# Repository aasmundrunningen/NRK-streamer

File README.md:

# NRK-streamer
A computer with a HDMI switch connected so that you can play NRK with one button press and switch to another HDMI input using a HDMI-switch

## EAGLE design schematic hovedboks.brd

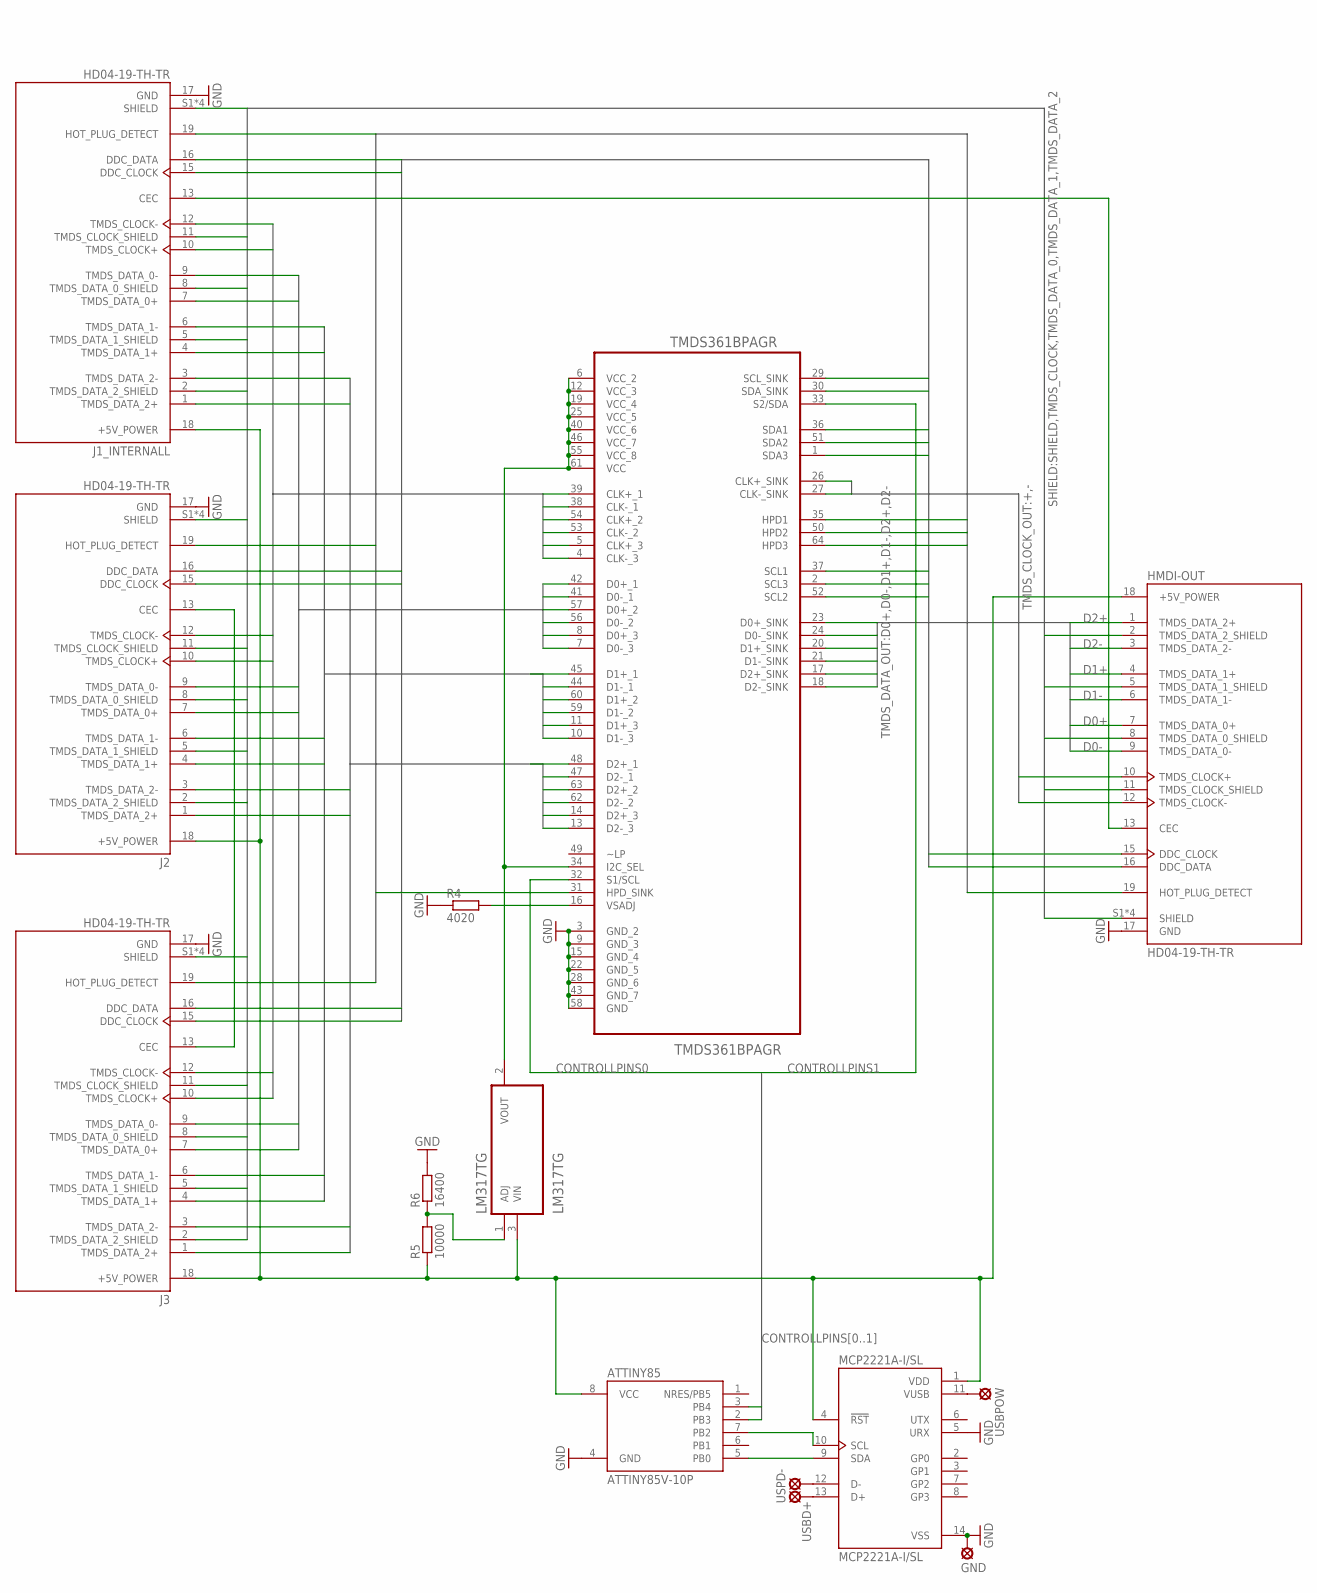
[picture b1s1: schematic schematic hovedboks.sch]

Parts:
ATTINY85: ATTINY85V-10P; PDIP08_300MIL
GND: LSP10
HMDI-OUT: HD04-19-TH-TR; CUI_HD04-19-TH-TR
J1_INTERNALL, J2, J3: HD04-19-TH-TR; CUI_HD04-19-TH-TR
LM317TG: LM317TG; TO254P1054X470X1955-3
MCP2221A-I/SL: MCP2221A-I/SL; SOIC127P600X175-14N
R4: 4020; 0204/7
R5: 10000; 0204/7
R6: 16400; 0204/7
TMDS361BPAGR: TMDS361BPAGR; QFP50P1200X1200X120-64N
USBD+: LSP10
USBPOW: LSP10
USPD-: LSP10

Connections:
1: J1_INTERNALL.19 (HOT_PLUG_DETECT), TMDS361BPAGR.35 (HPD1)
1_CLOCK: J1_INTERNALL.15 (DDC_CLOCK), TMDS361BPAGR.37 (SCL1)
1_DATA: J1_INTERNALL.16 (DDC_DATA), TMDS361BPAGR.36 (SDA1)
2: J2.19 (HOT_PLUG_DETECT), TMDS361BPAGR.50 (HPD2)
2_CLOCK: J2.15 (DDC_CLOCK), TMDS361BPAGR.2 (SCL3)
2_DATA: J2.16 (DDC_DATA), TMDS361BPAGR.51 (SDA2)
3: J3.19 (HOT_PLUG_DETECT), TMDS361BPAGR.64 (HPD3)
3_CLOCK: J3.15 (DDC_CLOCK), TMDS361BPAGR.52 (SCL2)
3_DATA: J3.16 (DDC_DATA), TMDS361BPAGR.1 (SDA3)
5V: ATTINY85.8 (VCC), HMDI-OUT.18 (+5V_POWER), J1_INTERNALL.18 (+5V_POWER), J2.18 (+5V_POWER), J3.18 (+5V_POWER), LM317TG.3 (VIN), MCP2221A-I/SL.1 (VDD), MCP2221A-I/SL.4 (!RST), R5.1
+: HMDI-OUT.10 (TMDS_CLOCK+), TMDS361BPAGR.26 (CLK+_SINK)
+1: J1_INTERNALL.1 (TMDS_DATA_2+), J1_INTERNALL.4 (TMDS_DATA_1+), J1_INTERNALL.7 (TMDS_DATA_0+), J1_INTERNALL.10 (TMDS_CLOCK+), J3.10 (TMDS_CLOCK+), TMDS361BPAGR.39 (CLK+_1), TMDS361BPAGR.42 (D0+_1), TMDS361BPAGR.45 (D1+_1), TMDS361BPAGR.48 (D2+_1)
+2: J2.1 (TMDS_DATA_2+), J2.4 (TMDS_DATA_1+), J2.7 (TMDS_DATA_0+), J2.10 (TMDS_CLOCK+), TMDS361BPAGR.54 (CLK+_2), TMDS361BPAGR.57 (D0+_2), TMDS361BPAGR.60 (D1+_2), TMDS361BPAGR.63 (D2+_2)
+3: J3.1 (TMDS_DATA_2+), J3.4 (TMDS_DATA_1+), J3.7 (TMDS_DATA_0+), TMDS361BPAGR.5 (CLK+_3), TMDS361BPAGR.8 (D0+_3), TMDS361BPAGR.11 (D1+_3), TMDS361BPAGR.14 (D2+_3)
-: HMDI-OUT.12 (TMDS_CLOCK-), TMDS361BPAGR.27 (CLK-_SINK)
-1: J1_INTERNALL.3 (TMDS_DATA_2-), J1_INTERNALL.6 (TMDS_DATA_1-), J1_INTERNALL.9 (TMDS_DATA_0-), J1_INTERNALL.12 (TMDS_CLOCK-), J3.12 (TMDS_CLOCK-), TMDS361BPAGR.38 (CLK-_1), TMDS361BPAGR.41 (D0-_1), TMDS361BPAGR.44 (D1-_1), TMDS361BPAGR.47 (D2-_1)
-2: J2.3 (TMDS_DATA_2-), J2.6 (TMDS_DATA_1-), J2.9 (TMDS_DATA_0-), J2.12 (TMDS_CLOCK-), TMDS361BPAGR.53 (CLK-_2), TMDS361BPAGR.56 (D0-_2), TMDS361BPAGR.59 (D1-_2), TMDS361BPAGR.62 (D2-_2)
-3: J3.3 (TMDS_DATA_2-), J3.6 (TMDS_DATA_1-), J3.9 (TMDS_DATA_0-), TMDS361BPAGR.4 (CLK-_3), TMDS361BPAGR.7 (D0-_3), TMDS361BPAGR.10 (D1-_3), TMDS361BPAGR.13 (D2-_3)
CEC_INTERNAL-OUT: HMDI-OUT.13 (CEC), J1_INTERNALL.13 (CEC)
CONTROLLPINS0: ATTINY85.2 (PB3), TMDS361BPAGR.32 (S1/SCL)
CONTROLLPINS1: ATTINY85.3 (PB4), TMDS361BPAGR.33 (S2/SDA)
D0+: HMDI-OUT.7 (TMDS_DATA_0+), TMDS361BPAGR.23 (D0+_SINK)
D0-: HMDI-OUT.9 (TMDS_DATA_0-), TMDS361BPAGR.24 (D0-_SINK)
D1+: HMDI-OUT.4 (TMDS_DATA_1+), TMDS361BPAGR.20 (D1+_SINK)
D1-: HMDI-OUT.6 (TMDS_DATA_1-), TMDS361BPAGR.21 (D1-_SINK)
D2+: HMDI-OUT.1 (TMDS_DATA_2+), TMDS361BPAGR.17 (D2+_SINK)
D2-: HMDI-OUT.3 (TMDS_DATA_2-), TMDS361BPAGR.18 (D2-_SINK)
GND: ATTINY85.4 (GND), GND.MP, HMDI-OUT.17 (GND), J1_INTERNALL.17 (GND), J2.17 (GND), J3.17 (GND), MCP2221A-I/SL.5 (URX), MCP2221A-I/SL.14 (VSS), R4.1, R6.2, TMDS361BPAGR.3 (GND_2), TMDS361BPAGR.9 (GND_3), TMDS361BPAGR.15 (GND_4), TMDS361BPAGR.22 (GND_5), TMDS361BPAGR.28 (GND_6), TMDS361BPAGR.43 (GND_7), TMDS361BPAGR.58 (GND)
unnamed: J2.13 (CEC), J3.13 (CEC)
unnamed: LM317TG.2 (VOUT), TMDS361BPAGR.6 (VCC_2), TMDS361BPAGR.12 (VCC_3), TMDS361BPAGR.19 (VCC_4), TMDS361BPAGR.25 (VCC_5), TMDS361BPAGR.34 (I2C_SEL), TMDS361BPAGR.40 (VCC_6), TMDS361BPAGR.46 (VCC_7), TMDS361BPAGR.55 (VCC_8), TMDS361BPAGR.61 (VCC)
unnamed: LM317TG.1 (ADJ), R5.2, R6.1
unnamed: ATTINY85.5 (PB0), MCP2221A-I/SL.9 (SDA)
unnamed: ATTINY85.7 (PB2), MCP2221A-I/SL.10 (SCL)
unnamed: MCP2221A-I/SL.11 (VUSB), USBPOW.MP
unnamed: MCP2221A-I/SL.13 (D+), USBD+.MP
unnamed: MCP2221A-I/SL.12 (D-), USPD-.MP
unnamed: R4.2, TMDS361BPAGR.16 (VSADJ)
OUT: HMDI-OUT.19 (HOT_PLUG_DETECT), TMDS361BPAGR.31 (HPD_SINK)
OUT_CLOCK: HMDI-OUT.15 (DDC_CLOCK), TMDS361BPAGR.29 (SCL_SINK)
OUT_DATA: HMDI-OUT.16 (DDC_DATA), TMDS361BPAGR.30 (SDA_SINK)
SHIELD: HMDI-OUT.S1 (SHIELD), HMDI-OUT.S2 (SHIELD), HMDI-OUT.S3 (SHIELD), HMDI-OUT.S4 (SHIELD), J1_INTERNALL.S1 (SHIELD), J1_INTERNALL.S2 (SHIELD), J1_INTERNALL.S3 (SHIELD), J1_INTERNALL.S4 (SHIELD), J2.S1 (SHIELD), J2.S2 (SHIELD), J2.S3 (SHIELD), J2.S4 (SHIELD), J3.S1 (SHIELD), J3.S2 (SHIELD), J3.S3 (SHIELD), J3.S4 (SHIELD)
TMDS_CLOCK: HMDI-OUT.11 (TMDS_CLOCK_SHIELD), J1_INTERNALL.11 (TMDS_CLOCK_SHIELD), J2.11 (TMDS_CLOCK_SHIELD), J3.11 (TMDS_CLOCK_SHIELD)
TMDS_DATA_0: HMDI-OUT.8 (TMDS_DATA_0_SHIELD), J1_INTERNALL.8 (TMDS_DATA_0_SHIELD), J2.8 (TMDS_DATA_0_SHIELD), J3.8 (TMDS_DATA_0_SHIELD)
TMDS_DATA_1: HMDI-OUT.5 (TMDS_DATA_1_SHIELD), J1_INTERNALL.5 (TMDS_DATA_1_SHIELD), J2.5 (TMDS_DATA_1_SHIELD), J3.5 (TMDS_DATA_1_SHIELD)
TMDS_DATA_2: HMDI-OUT.2 (TMDS_DATA_2_SHIELD), J1_INTERNALL.2 (TMDS_DATA_2_SHIELD), J2.2 (TMDS_DATA_2_SHIELD), J3.2 (TMDS_DATA_2_SHIELD)

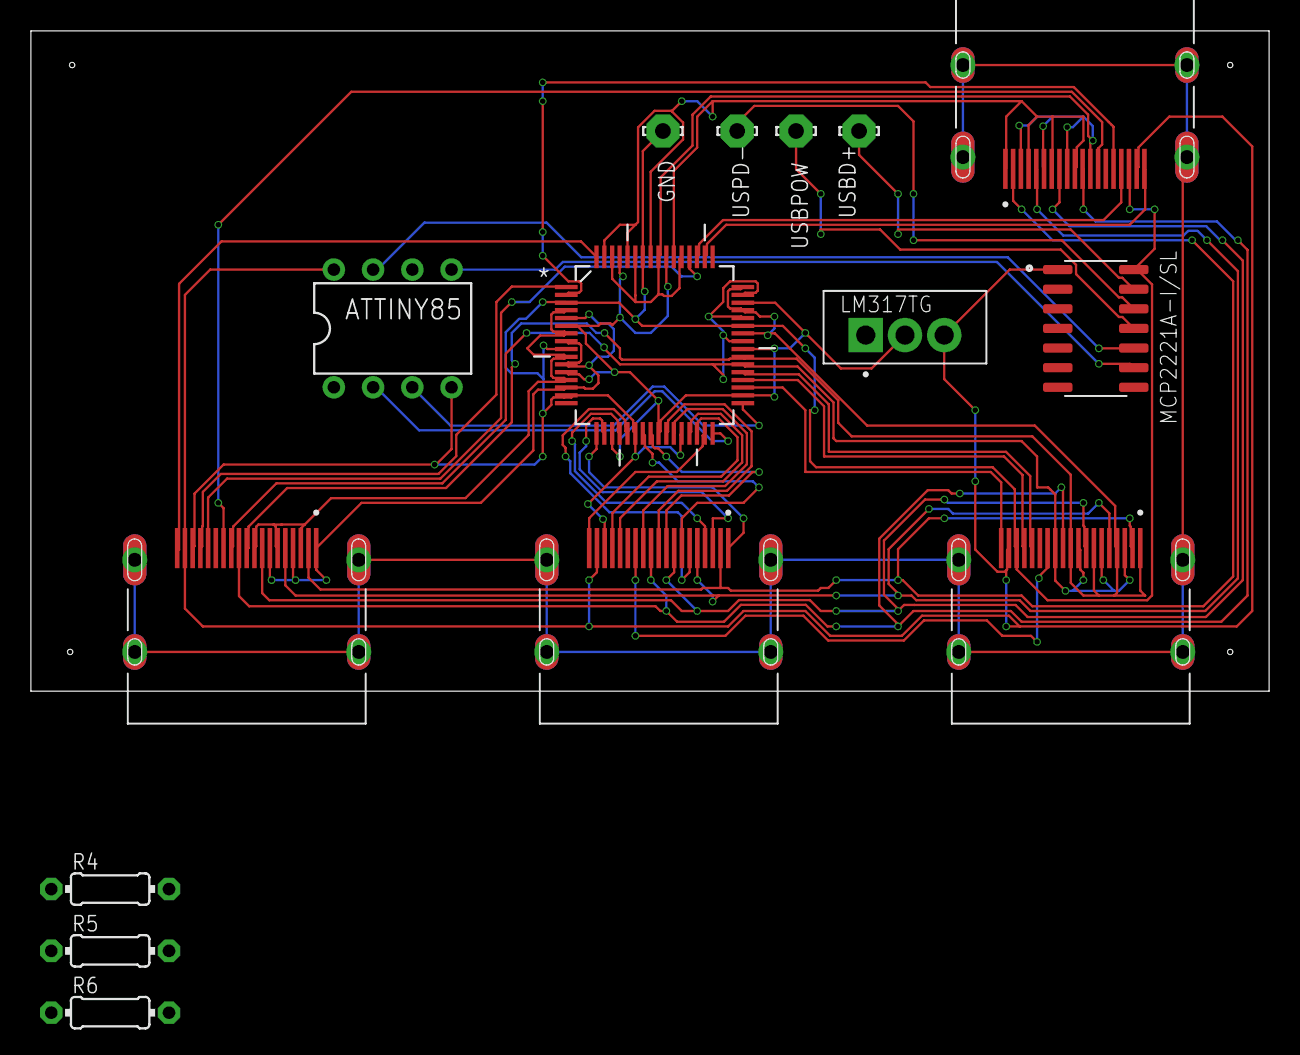
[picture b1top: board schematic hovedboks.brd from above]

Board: 2 copper layers, 80.2 x 42.7 mm, 15 parts (0 on the bottom side), 45 nets.

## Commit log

2023-03-18 raw copy of the original onedrive folder
2023-09-11 Opprettet med Colaboratory
